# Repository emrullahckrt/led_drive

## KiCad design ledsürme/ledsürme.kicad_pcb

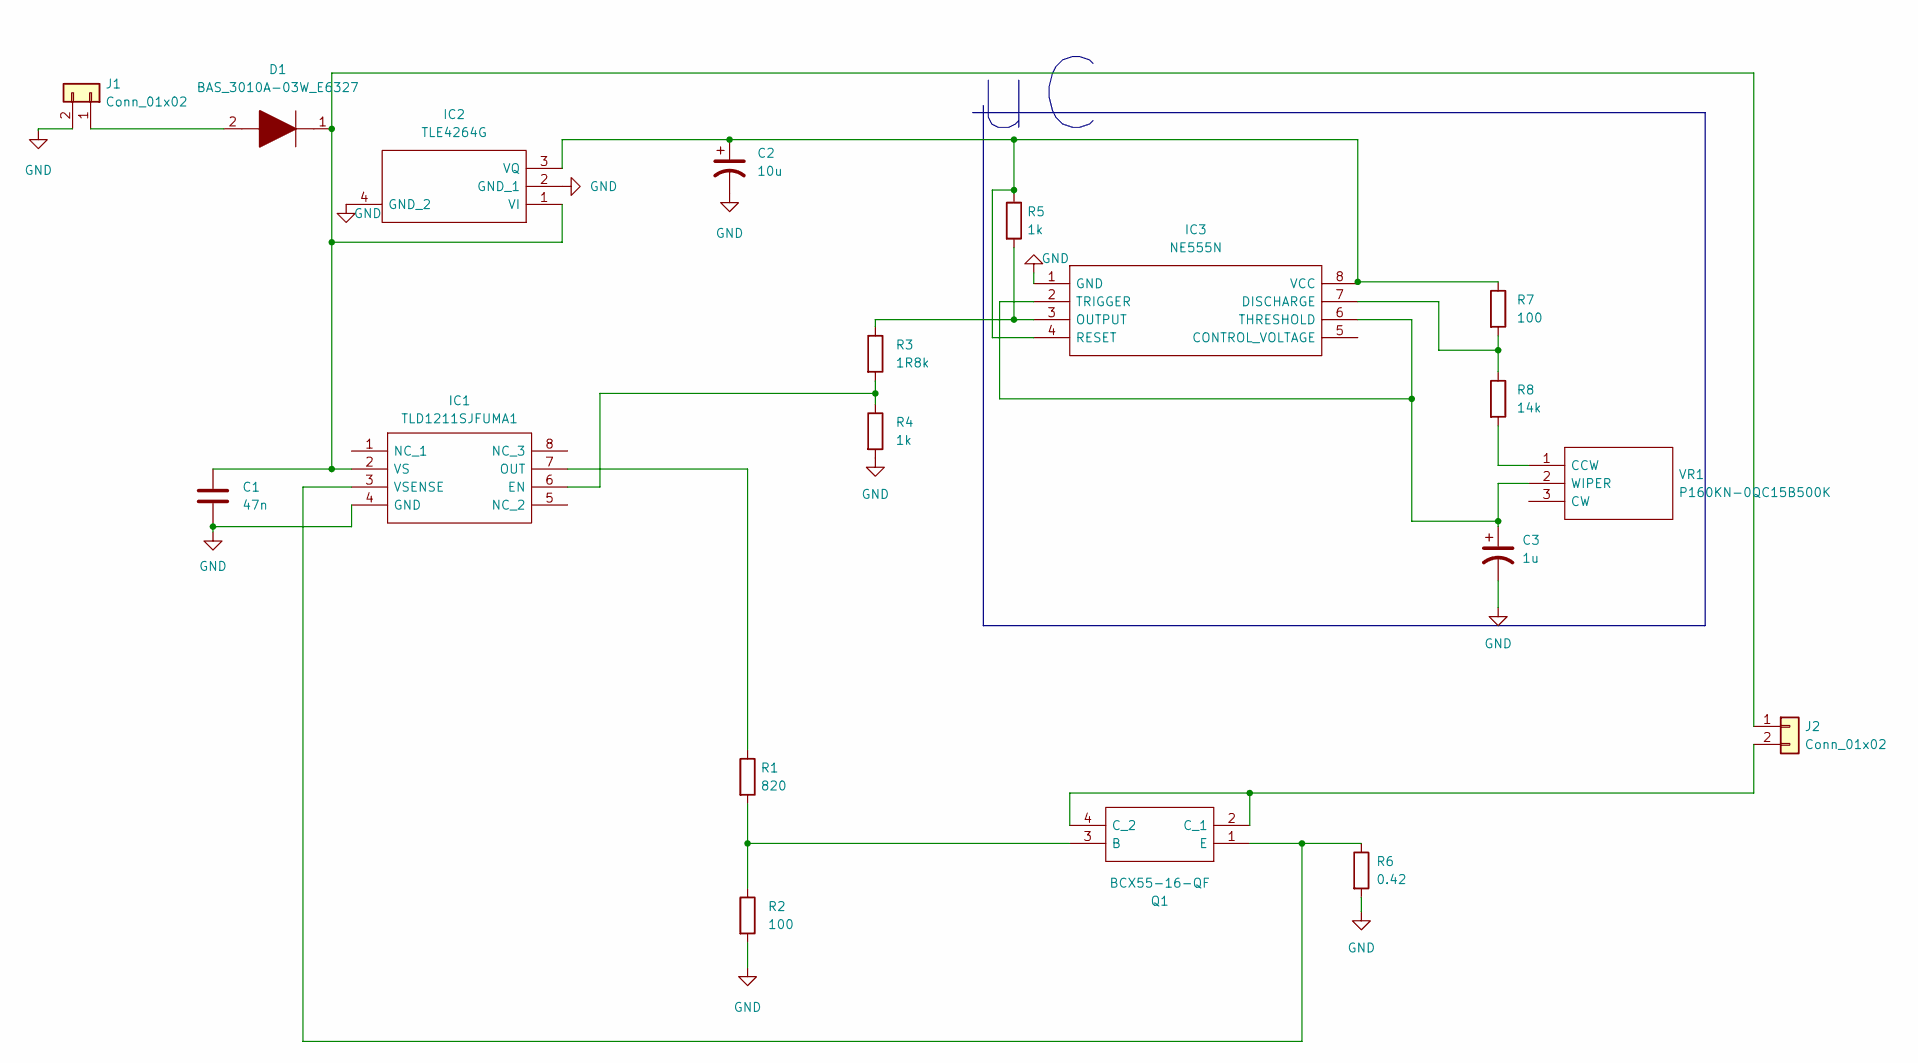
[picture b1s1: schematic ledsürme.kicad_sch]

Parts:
C1: 47n; C_Disc_D3.0mm_W2.0mm_P2.50mm
C2: 10u; CP_Radial_D10.0mm_P2.50mm
C3: 1u; CP_Radial_D10.0mm_P2.50mm
D1: BAS_3010A-03W_E6327; BAS30110A; Manufacturer_Part_Number BAS 3010A-03W E6327; Mouser Part Number 726-BAS3010A03WE6327
IC1: TLD1211SJFUMA1; TLD1211SJ; Manufacturer_Part_Number TLD1211SJFUMA1; Mouser Part Number 726-TLD1211SJFUMA1
IC2: TLE4264G; TLE4264; Manufacturer_Part_Number TLE4264G; Mouser Part Number 726-TLE4264G
IC3: NE555N; NE555N-PDIP; Manufacturer_Part_Number NE555N; Mouser Part Number 511-NE555N
J1, J2: Conn_01x02; PinHeader_1x02_P2.54mm_Vertical
Q1: BCX55-16-QF; BCX5516QF; Manufacturer_Part_Number BCX55-16-QF
R1: 820; R_Axial_DIN0309_L9.0mm_D3.2mm_P12.70mm_Horizontal
R2, R7: 100; R_Axial_DIN0309_L9.0mm_D3.2mm_P12.70mm_Horizontal
R3: 1R8k; R_Axial_DIN0309_L9.0mm_D3.2mm_P12.70mm_Horizontal
R4, R5: 1k; R_Axial_DIN0309_L9.0mm_D3.2mm_P12.70mm_Horizontal
R6: 0.42; R_Axial_DIN0309_L9.0mm_D3.2mm_P12.70mm_Horizontal
R8: 14k; R_Axial_DIN0309_L9.0mm_D3.2mm_P12.70mm_Horizontal
VR1: P160KN-0QC15B500K; P160KN0QC15B500K; Manufacturer_Part_Number P160KN-0QC15B500K; Mouser Part Number 858-P160KN0QC15B500K

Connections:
GND: C1.2, C2.2, C3.2, IC1.4 (GND), IC2.2 (GND_1), IC2.4 (GND_2), IC3.1 (GND), J1.2, R2.2, R4.2, R6.2
unnamed: C1.1, D1.1, IC1.2 (VS), IC2.1 (VI), J2.1
unnamed: C2.1, IC2.3 (VQ), IC3.4 (RESET), IC3.8 (VCC), R5.1, R7.1
unnamed: C3.1, IC3.2 (TRIGGER), IC3.6 (THRESHOLD), VR1.2 (WIPER)
unnamed: D1.2, J1.1
unnamed: IC1.3 (VSENSE), Q1.1 (E), R6.1
unnamed: IC1.6 (EN), R3.2, R4.1
unnamed: IC1.7 (OUT), R1.1
unnamed: IC3.3 (OUTPUT), R3.1, R5.2
unnamed: IC3.7 (DISCHARGE), R7.2, R8.1
unnamed: J2.2, Q1.2 (C_1), Q1.4 (C_2)
unnamed: Q1.3 (B), R1.2, R2.1
unnamed: R8.2, VR1.1 (CCW)

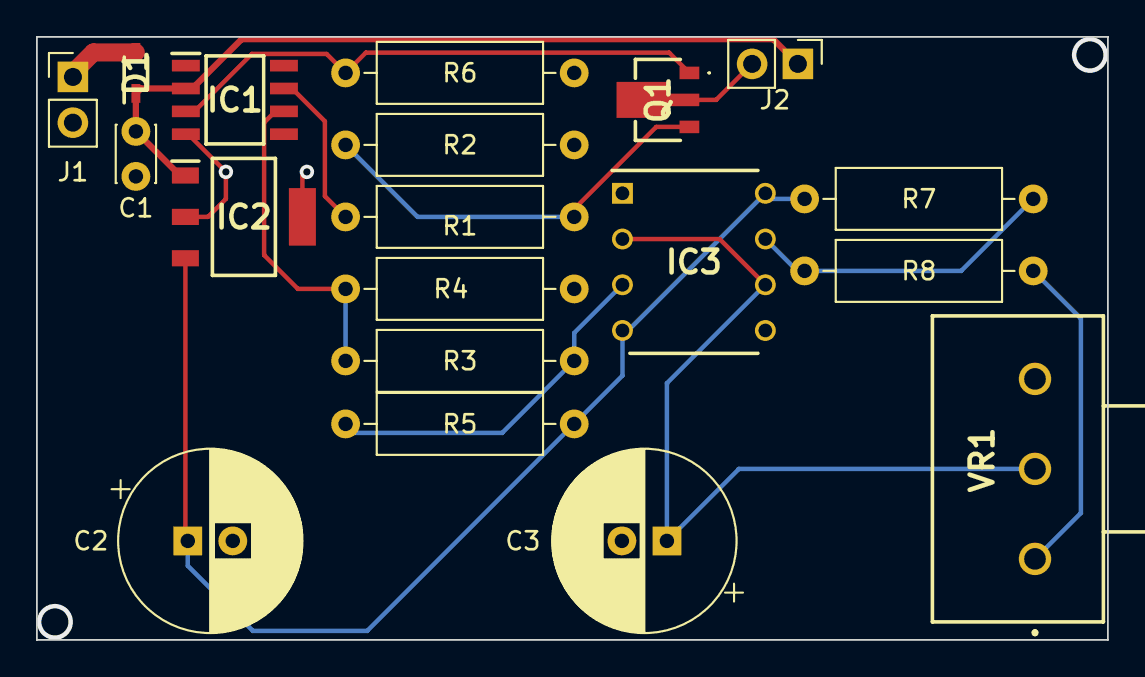
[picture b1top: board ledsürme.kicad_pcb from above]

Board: 2 copper layers, 59.5 x 33.5 mm, 19 parts (0 on the bottom side), 13 nets.

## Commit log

2024-02-23 led_drive
    led drive with n555
